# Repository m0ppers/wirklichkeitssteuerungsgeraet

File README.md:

# Wirklichkeitssteuerungsgeraet

(Key) components used to realize "Wirklichkeitssteuerungsgeraet" released at revision 2017 as part of the wild compo (modified game files are not contained)

(Un)license is UNLICENSE

Parts (well the initial code) of `amiga-gamepad` was derived from one of the ft90x examples so their restrictions apply (see code for details).

This is also a wild (heh) language zoo :D

## Components

- amiga-joystick-click-board

    Simple Kicad pcb for joystick2USB click board on top of the ft90x clicker2
    BEWARE: I THINK I found out during soldering that I made a classic of by one error. Be sure to recount the rows and compare it with the clicker if you are really reproducing this.

- amiga-gamepad

    Firmware for a clicker2 ft90x. This will create a full USB Gamepad from an Amiga Joystick connected to a clicker2 ft90x having a `amiga-joystick-click-board`.
    The code can be compiled using the official FTDI 90x toolchain + cmake. This is actually completely useable (and maybe even useful?) standalone. Tested on Windows and Android.

- credits

    Code used to create the credits. SVG+CSS

- font

    Reengineered font from cycles the game. Done using http://www.pentacom.jp/pentacom/bitfontmaker2/ (super awesome tool!)

- firmware

    Arduino code for the BMW <=> Amiga Joystick translation :D Upload to the Arduino micro

- hardware

  Simple fritzing layout of wirklichkeitssteuerungsgeraet. This was quickly put together at the party and is not to be trusted. Also some parts are missing because I fail to create
  proper parts in fritzing. The real MCP2515 also has CAN L and CAN H. These should be connected to the motorcycle connector. You also have to apply a 120 Ohm resistor to the CAN§
  wiring (the speedometer is a terminating node) - the resistor should be available on your board. Once assembled this thing should be connected to the amiga-joystick-click-board :)

- logo

    The logo :S Code is more or less completely stolen from here: https://www.reaktor.com/blog/crash-course-to-amiga-assembly-programming/
    The in game variant had to be slightly adjusted to make it play well with the rest

- png2amiga

    Super hackish (my rust is super bad :() tool to convert an image with a fixed PNG palette to an raw Amiga image

## External components

- brumm case (https://github.com/m0ppers/brumm-case)
- RPck file archiver (https://github.com/m0ppers/rpck)

## Necessary hardware

Please note that the hardware components are not chosen because they were well suited for the job but because I had them at home :D (and I could finally put the otherwise useless clicker2 board to good use :D). From scratch I would probably just  use 1 ExploreEmbedded M3 board (https://www.exploreembedded.com/blog/new-product-announcements/explore-m3-this-board-is-more-about-learning-than-anything-else/) because it has everything on board (except for the bosch sensor) that is needed here. Their support is super awesome as well.

The actual hardware:

- clicker2 ft90x (https://www.mikroe.com/ft90x/) for the Joystick2USB Gamepad part

    Please note that this is good but SUPER proprietary hardware. I bought it because I needed a cheap dev board for the ft90x. They even try to crosssell their (proprietary) compiler (lol :S). Also it is a pain to get the code onboard the chip (I used the proprietary FTDI programmer that costs ~30 EUR).

- Arduino micro (https://www.arduino.cc/en/Main/ArduinoBoardMicro)

    On pictures you will see that I am not using an original one. I bought a iteaduino nano. Do not support these *** (had trouble the second time). Their support is super @^@Q#$@$. Buy genuine. Be cool unlike me.

- MCP2515 board (https://www.aliexpress.com/wholesale?catId=0&initiative_id=SB_20170317132251&SearchText=MCP2515)
- Adafruit BNO055 breakout board (http://www.exp-tech.de/adafruit-9-dof-absolute-orientation-imu-fusion-breakout-bno055)

## BMW Connector

The information about the BMW connector is licensed under a different license:
```
/*
* ----------------------------------------------------------------------------
* "THE BEER-WARE LICENSE" (Revision 42):
* <andreas@mop.koeln> searched the internet. As long as you retain this notice you
* can do whatever you want with this stuff. If we meet some day, and you think
* this stuff is worth it, you can buy me a beer in return Poul-Henning Kamp
* ----------------------------------------------------------------------------
*/
```

The connectors are:

http://www.mouser.de/pdfdocs/ENG_CS_13079993_Micro_Quadlok__1211_13079993.PDF

    Female: 1-967616-1
    Male:  1-967587-3

(Seriously. It took me hours to find that. You DO owe me a beer if you found this info helpful).

## Acknowledgments

- http://mrjester.hapisan.com/04_MC68/ is invaluable for any n00b starting m68k assembly
- https://www.reaktor.com/blog/crash-course-to-amiga-assembly-programming/
- BMW CAN Reversing (https://docs.google.com/spreadsheets/d/1tUrOES5fQZa92Robr6uP8v2dzQDq9ohHjUiTU3isqdc/edit#gid=0)
- Wanted Teams rpck decruncher (http://wt.exotica.org.uk/others.html) made me understand the rpck format. They are still active :D

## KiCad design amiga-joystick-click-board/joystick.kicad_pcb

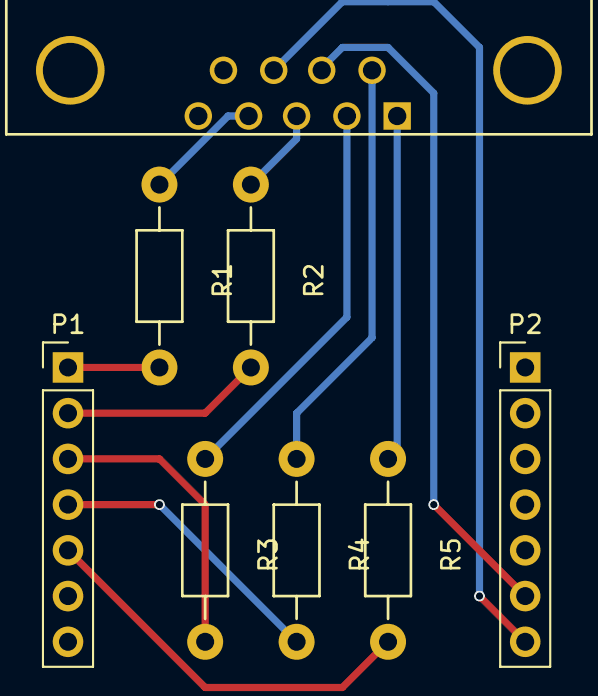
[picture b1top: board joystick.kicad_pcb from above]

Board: 2 copper layers, 8 parts (0 on the bottom side), 12 nets.

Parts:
J1: DB9; DB9MC
P1, P2: CONN_01X07; Pin_Header_Straight_1x07_Pitch2.54mm
R1, R2, R3, R4, R5: R; Resistor_Horizontal_RM10mm

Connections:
unnamed: J1.1, R5.1
unnamed: J1.2, R3.1
unnamed: J1.3, R2.1
unnamed: J1.4, R1.1
unnamed: J1.6, R4.1
unnamed: J1.7, P2.6
unnamed: J1.8, P2.7
unnamed: P1.1, R1.2
unnamed: P1.2, R2.2
unnamed: P1.3, R3.2
unnamed: P1.4, R4.2
unnamed: P1.5, R5.2

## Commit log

2017-03-19 Yo...weiss auch nit warum alle immer mit der deadline kaempfen
2017-03-19 fail negative values
2017-04-01 rename so arduino IDE doesn't go crazy
2017-04-08 Sensor change
2017-04-08 MUSIC
2017-04-16 add basic fritzing layout
2017-04-16 Add GND and VCC lines
2017-04-16 add connector and some readme
2017-04-16 A bit more prosa
